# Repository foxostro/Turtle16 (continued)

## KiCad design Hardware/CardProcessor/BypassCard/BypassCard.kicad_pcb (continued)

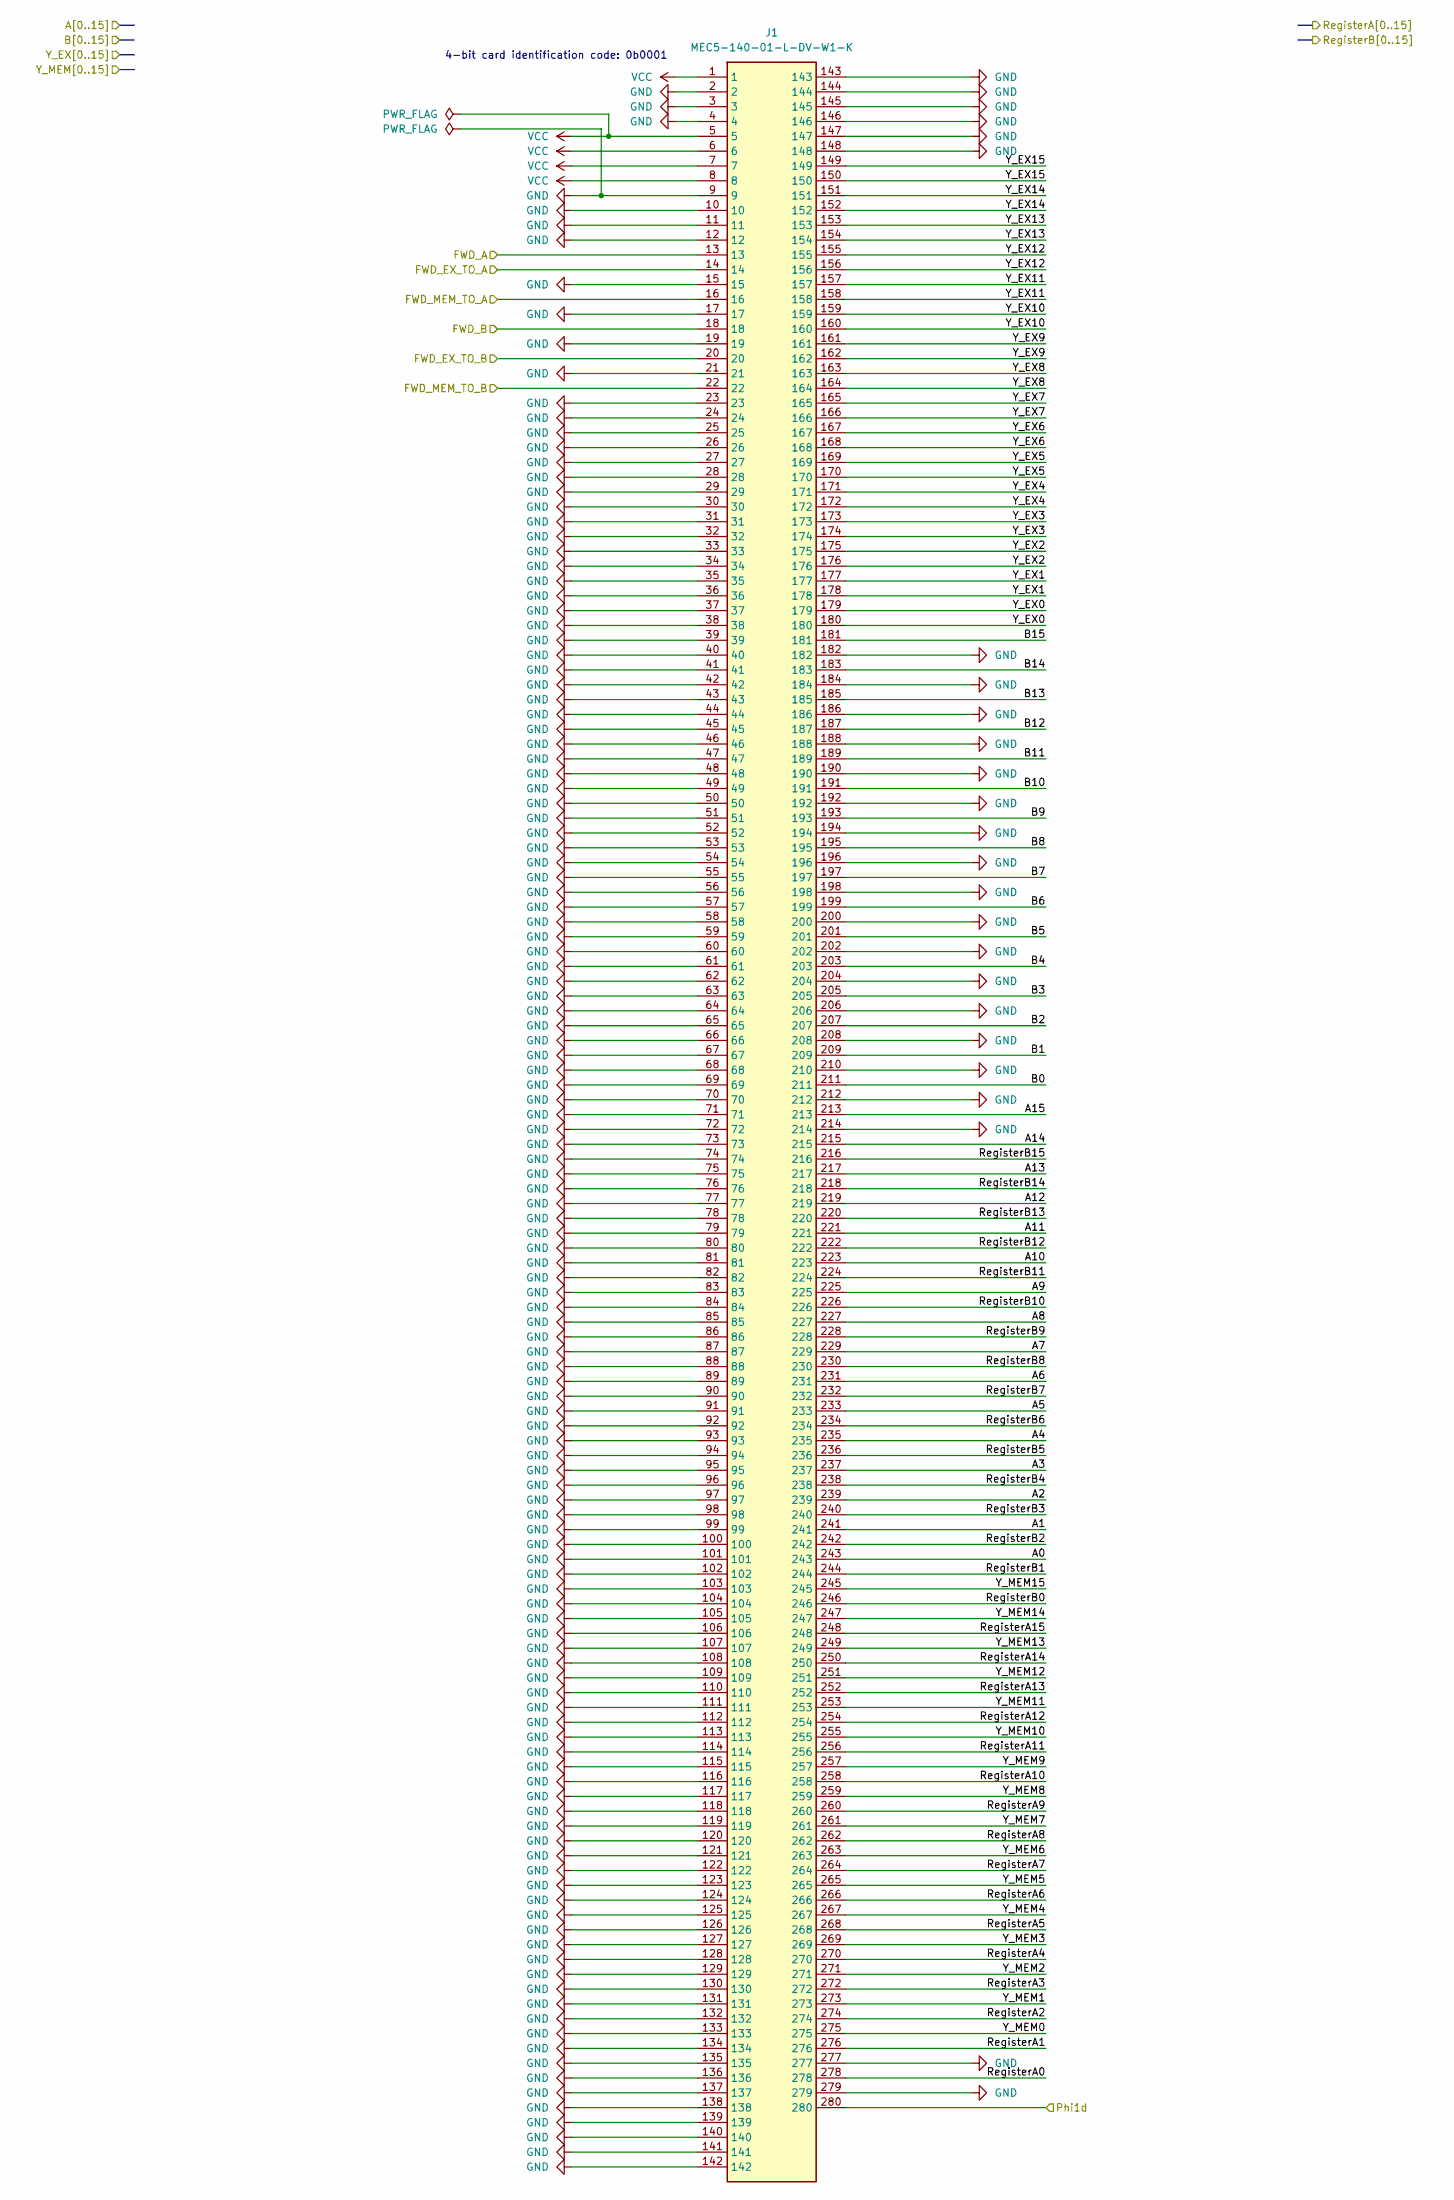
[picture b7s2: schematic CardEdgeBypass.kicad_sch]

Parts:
J1: MEC5-140-01-L-DV-W1-K; MEC5-140-01-L-DV-W1-K_Edge; Mouser Part Number 200-MEC514001LDVW1K

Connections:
/Bypass Module/A0: J1.243; also elsewhere on the board
/Bypass Module/A1: J1.241; also elsewhere on the board
/Bypass Module/A2: J1.239; also elsewhere on the board
/Bypass Module/A3: J1.237; also elsewhere on the board
/Bypass Module/A4: J1.235; also elsewhere on the board
/Bypass Module/A5: J1.233; also elsewhere on the board
/Bypass Module/A6: J1.231; also elsewhere on the board
/Bypass Module/A7: J1.229; also elsewhere on the board
/Bypass Module/A8: J1.227; also elsewhere on the board
/Bypass Module/A9: J1.225; also elsewhere on the board
/Bypass Module/A10: J1.223; also elsewhere on the board
/Bypass Module/A11: J1.221; also elsewhere on the board
/Bypass Module/A12: J1.219; also elsewhere on the board
/Bypass Module/A13: J1.217; also elsewhere on the board
/Bypass Module/A14: J1.215; also elsewhere on the board
/Bypass Module/A15: J1.213; also elsewhere on the board
/Bypass Module/B0: J1.211; also elsewhere on the board
/Bypass Module/B1: J1.209; also elsewhere on the board
/Bypass Module/B2: J1.207; also elsewhere on the board
/Bypass Module/B3: J1.205; also elsewhere on the board
/Bypass Module/B4: J1.203; also elsewhere on the board
/Bypass Module/B5: J1.201; also elsewhere on the board
/Bypass Module/B6: J1.199; also elsewhere on the board
/Bypass Module/B7: J1.197; also elsewhere on the board
/Bypass Module/B8: J1.195; also elsewhere on the board
/Bypass Module/B9: J1.193; also elsewhere on the board
/Bypass Module/B10: J1.191; also elsewhere on the board
/Bypass Module/B11: J1.189; also elsewhere on the board
/Bypass Module/B12: J1.187; also elsewhere on the board
/Bypass Module/B13: J1.185; also elsewhere on the board
/Bypass Module/B14: J1.183; also elsewhere on the board
/Bypass Module/B15: J1.181; also elsewhere on the board
/Bypass Module/FWD_A: J1.13; also elsewhere on the board
/Bypass Module/FWD_B: J1.18; also elsewhere on the board
/Bypass Module/FWD_EX_TO_A: J1.16; also elsewhere on the board
/Bypass Module/FWD_EX_TO_B: J1.20; also elsewhere on the board
/Bypass Module/FWD_MEM_TO_A: J1.14; also elsewhere on the board
/Bypass Module/FWD_MEM_TO_B: J1.22; also elsewhere on the board
/Bypass Module/Phi1d: J1.280; also elsewhere on the board
/Bypass Module/RegisterA0: J1.278; also elsewhere on the board
/Bypass Module/RegisterA1: J1.276; also elsewhere on the board
/Bypass Module/RegisterA2: J1.274; also elsewhere on the board
/Bypass Module/RegisterA3: J1.272; also elsewhere on the board
/Bypass Module/RegisterA4: J1.270; also elsewhere on the board
/Bypass Module/RegisterA5: J1.268; also elsewhere on the board
/Bypass Module/RegisterA6: J1.266; also elsewhere on the board
/Bypass Module/RegisterA7: J1.264; also elsewhere on the board
/Bypass Module/RegisterA8: J1.262; also elsewhere on the board
/Bypass Module/RegisterA9: J1.260; also elsewhere on the board
/Bypass Module/RegisterA10: J1.258; also elsewhere on the board
/Bypass Module/RegisterA11: J1.256; also elsewhere on the board
/Bypass Module/RegisterA12: J1.254; also elsewhere on the board
/Bypass Module/RegisterA13: J1.252; also elsewhere on the board
/Bypass Module/RegisterA14: J1.250; also elsewhere on the board
/Bypass Module/RegisterA15: J1.248; also elsewhere on the board
/Bypass Module/RegisterB0: J1.246; also elsewhere on the board
/Bypass Module/RegisterB1: J1.244; also elsewhere on the board
/Bypass Module/RegisterB2: J1.242; also elsewhere on the board
/Bypass Module/RegisterB3: J1.240; also elsewhere on the board
/Bypass Module/RegisterB4: J1.238; also elsewhere on the board
/Bypass Module/RegisterB5: J1.236; also elsewhere on the board
/Bypass Module/RegisterB6: J1.234; also elsewhere on the board
/Bypass Module/RegisterB7: J1.232; also elsewhere on the board
/Bypass Module/RegisterB8: J1.230; also elsewhere on the board
/Bypass Module/RegisterB9: J1.228; also elsewhere on the board
/Bypass Module/RegisterB10: J1.226; also elsewhere on the board
/Bypass Module/RegisterB11: J1.224; also elsewhere on the board
/Bypass Module/RegisterB12: J1.222; also elsewhere on the board
/Bypass Module/RegisterB13: J1.220; also elsewhere on the board
/Bypass Module/RegisterB14: J1.218; also elsewhere on the board
/Bypass Module/RegisterB15: J1.216; also elsewhere on the board
/Bypass Module/Y_EX0: J1.179, J1.180; also elsewhere on the board
/Bypass Module/Y_EX1: J1.177, J1.178; also elsewhere on the board
/Bypass Module/Y_EX2: J1.175, J1.176; also elsewhere on the board
/Bypass Module/Y_EX3: J1.173, J1.174; also elsewhere on the board
/Bypass Module/Y_EX4: J1.171, J1.172; also elsewhere on the board
/Bypass Module/Y_EX5: J1.169, J1.170; also elsewhere on the board
/Bypass Module/Y_EX6: J1.167, J1.168; also elsewhere on the board
/Bypass Module/Y_EX7: J1.165, J1.166; also elsewhere on the board
/Bypass Module/Y_EX8: J1.163, J1.164; also elsewhere on the board
/Bypass Module/Y_EX9: J1.161, J1.162; also elsewhere on the board
/Bypass Module/Y_EX10: J1.159, J1.160; also elsewhere on the board
/Bypass Module/Y_EX11: J1.157, J1.158; also elsewhere on the board
/Bypass Module/Y_EX12: J1.155, J1.156; also elsewhere on the board
/Bypass Module/Y_EX13: J1.153, J1.154; also elsewhere on the board
/Bypass Module/Y_EX14: J1.151, J1.152; also elsewhere on the board
/Bypass Module/Y_EX15: J1.149, J1.150; also elsewhere on the board
/Bypass Module/Y_MEM0: J1.275; also elsewhere on the board
/Bypass Module/Y_MEM1: J1.273; also elsewhere on the board
/Bypass Module/Y_MEM2: J1.271; also elsewhere on the board
/Bypass Module/Y_MEM3: J1.269; also elsewhere on the board
/Bypass Module/Y_MEM4: J1.267; also elsewhere on the board
/Bypass Module/Y_MEM5: J1.265; also elsewhere on the board
/Bypass Module/Y_MEM6: J1.263; also elsewhere on the board
/Bypass Module/Y_MEM7: J1.261; also elsewhere on the board
/Bypass Module/Y_MEM8: J1.259; also elsewhere on the board
/Bypass Module/Y_MEM9: J1.257; also elsewhere on the board
/Bypass Module/Y_MEM10: J1.255; also elsewhere on the board
/Bypass Module/Y_MEM11: J1.253; also elsewhere on the board
/Bypass Module/Y_MEM12: J1.251; also elsewhere on the board
/Bypass Module/Y_MEM13: J1.249; also elsewhere on the board
/Bypass Module/Y_MEM14: J1.247; also elsewhere on the board
/Bypass Module/Y_MEM15: J1.245; also elsewhere on the board
GND: J1.2, J1.3, J1.4, J1.9, J1.10, J1.11, J1.12, J1.15, J1.17, J1.19, J1.21, J1.23, J1.24, J1.25, J1.26, J1.27, J1.28, J1.29, J1.30, J1.31, J1.32, J1.33, J1.34, J1.35, J1.36, J1.37, J1.38, J1.39, J1.40, J1.41, J1.42, J1.43, J1.44, J1.45, J1.46, J1.47, J1.48, J1.49, J1.50, J1.51, J1.52, J1.53, J1.54, J1.55, J1.56, J1.57, J1.58, J1.59, J1.60, J1.61, J1.62, J1.63, J1.64, J1.65, J1.66, J1.67, J1.68, J1.69, J1.70, J1.71, J1.72, J1.73, J1.74, J1.75, J1.76, J1.77, J1.78, J1.79, J1.80, J1.81, J1.82, J1.83, J1.84, J1.85, J1.86, J1.87, J1.88, J1.89, J1.90, J1.91, J1.92, J1.93, J1.94, J1.95, J1.96, J1.97, J1.98, J1.99, J1.100, J1.101, J1.102, J1.103, J1.104, J1.105, J1.106, J1.107, J1.108, J1.109, J1.110, J1.111, J1.112, J1.113, J1.114, J1.115, J1.116, J1.117, J1.118, J1.119, J1.120, J1.121, J1.122, J1.123, J1.124, J1.125, J1.126, J1.127, J1.128, J1.129, J1.130, J1.131, J1.132, J1.133, J1.134, J1.135, J1.136, J1.137, J1.138, J1.139, J1.140, J1.141, J1.142, J1.143, J1.144, J1.145, J1.146, J1.147, J1.148, J1.182, J1.184, J1.186, J1.188, J1.190, J1.192, J1.194, J1.196, J1.198, J1.200, J1.202, J1.204, J1.206, J1.208, J1.210, J1.212, J1.214, J1.277, J1.279; also elsewhere on the board
VCC: J1.1, J1.5, J1.6, J1.7, J1.8; also elsewhere on the board

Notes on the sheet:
4-bit card identification code: 0b0001

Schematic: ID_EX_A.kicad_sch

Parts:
C7: 0.1uF; C_0603_1608Metric; Manufacturer# EMK107B7104KAHT; Mouser# 963-EMK107B7104KAHT
U7: 74ABT16374; TSSOP-48_6.1x12.5mm_P0.5mm; Manufacturer# SN74ABT16374ADGGR; Mouser# 595-SNABT16374ADGGR

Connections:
/Bypass Module/A0: U7.2 (1Q1); also elsewhere on the board
/Bypass Module/A1: U7.3 (1Q2); also elsewhere on the board
/Bypass Module/A2: U7.5 (1Q3); also elsewhere on the board
/Bypass Module/A3: U7.6 (1Q4); also elsewhere on the board
/Bypass Module/A4: U7.8 (1Q5); also elsewhere on the board
/Bypass Module/A5: U7.9 (1Q6); also elsewhere on the board
/Bypass Module/A6: U7.11 (1Q7); also elsewhere on the board
/Bypass Module/A7: U7.12 (1Q8); also elsewhere on the board
/Bypass Module/A8: U7.13 (2Q1); also elsewhere on the board
/Bypass Module/A9: U7.14 (2Q2); also elsewhere on the board
/Bypass Module/A10: U7.16 (2Q3); also elsewhere on the board
/Bypass Module/A11: U7.17 (2Q4); also elsewhere on the board
/Bypass Module/A12: U7.19 (2Q5); also elsewhere on the board
/Bypass Module/A13: U7.20 (2Q6); also elsewhere on the board
/Bypass Module/A14: U7.22 (2Q7); also elsewhere on the board
/Bypass Module/A15: U7.23 (2Q8); also elsewhere on the board
/Bypass Module/Operand Forwarding A/A_ID0: U7.47 (1D1); also elsewhere on the board
/Bypass Module/Operand Forwarding A/A_ID1: U7.46 (1D2); also elsewhere on the board
/Bypass Module/Operand Forwarding A/A_ID2: U7.44 (1D3); also elsewhere on the board
/Bypass Module/Operand Forwarding A/A_ID3: U7.43 (1D4); also elsewhere on the board
/Bypass Module/Operand Forwarding A/A_ID4: U7.41 (1D5); also elsewhere on the board
/Bypass Module/Operand Forwarding A/A_ID5: U7.40 (1D6); also elsewhere on the board
/Bypass Module/Operand Forwarding A/A_ID6: U7.38 (1D7); also elsewhere on the board
/Bypass Module/Operand Forwarding A/A_ID7: U7.37 (1D8); also elsewhere on the board
/Bypass Module/Operand Forwarding A/A_ID8: U7.36 (2D1); also elsewhere on the board
/Bypass Module/Operand Forwarding A/A_ID9: U7.35 (2D2); also elsewhere on the board
/Bypass Module/Operand Forwarding A/A_ID10: U7.33 (2D3); also elsewhere on the board
/Bypass Module/Operand Forwarding A/A_ID11: U7.32 (2D4); also elsewhere on the board
/Bypass Module/Operand Forwarding A/A_ID12: U7.30 (2D5); also elsewhere on the board
/Bypass Module/Operand Forwarding A/A_ID13: U7.29 (2D6); also elsewhere on the board
/Bypass Module/Operand Forwarding A/A_ID14: U7.27 (2D7); also elsewhere on the board
/Bypass Module/Operand Forwarding A/A_ID15: U7.26 (2D8); also elsewhere on the board
/Bypass Module/Phi1d: U7.25 (2CLK), U7.48 (1CLK); also elsewhere on the board
GND: C7.2, U7.1 (1~OE), U7.4 (GND), U7.10 (GND), U7.15 (GND), U7.21 (GND), U7.24 (2~OE), U7.28 (GND), U7.34 (GND), U7.39 (GND), U7.45 (GND); also elsewhere on the board
VCC: C7.1, U7.7 (VCC), U7.18 (VCC), U7.31 (VCC), U7.42 (VCC); also elsewhere on the board

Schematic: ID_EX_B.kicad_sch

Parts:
C8: 0.1uF; C_0603_1608Metric; Manufacturer# EMK107B7104KAHT; Mouser# 963-EMK107B7104KAHT
U8: 74ABT16374; TSSOP-48_6.1x12.5mm_P0.5mm; Manufacturer# SN74ABT16374ADGGR; Mouser# 595-SNABT16374ADGGR

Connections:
/Bypass Module/B0: U8.2 (1Q1); also elsewhere on the board
/Bypass Module/B1: U8.3 (1Q2); also elsewhere on the board
/Bypass Module/B2: U8.5 (1Q3); also elsewhere on the board
/Bypass Module/B3: U8.6 (1Q4); also elsewhere on the board
/Bypass Module/B4: U8.8 (1Q5); also elsewhere on the board
/Bypass Module/B5: U8.9 (1Q6); also elsewhere on the board
/Bypass Module/B6: U8.11 (1Q7); also elsewhere on the board
/Bypass Module/B7: U8.12 (1Q8); also elsewhere on the board
/Bypass Module/B8: U8.13 (2Q1); also elsewhere on the board
/Bypass Module/B9: U8.14 (2Q2); also elsewhere on the board
/Bypass Module/B10: U8.16 (2Q3); also elsewhere on the board
/Bypass Module/B11: U8.17 (2Q4); also elsewhere on the board
/Bypass Module/B12: U8.19 (2Q5); also elsewhere on the board
/Bypass Module/B13: U8.20 (2Q6); also elsewhere on the board
/Bypass Module/B14: U8.22 (2Q7); also elsewhere on the board
/Bypass Module/B15: U8.23 (2Q8); also elsewhere on the board
/Bypass Module/Operand Forwarding B/B_ID0: U8.47 (1D1); also elsewhere on the board
/Bypass Module/Operand Forwarding B/B_ID1: U8.46 (1D2); also elsewhere on the board
/Bypass Module/Operand Forwarding B/B_ID2: U8.44 (1D3); also elsewhere on the board
/Bypass Module/Operand Forwarding B/B_ID3: U8.43 (1D4); also elsewhere on the board
/Bypass Module/Operand Forwarding B/B_ID4: U8.41 (1D5); also elsewhere on the board
/Bypass Module/Operand Forwarding B/B_ID5: U8.40 (1D6); also elsewhere on the board
/Bypass Module/Operand Forwarding B/B_ID6: U8.38 (1D7); also elsewhere on the board
/Bypass Module/Operand Forwarding B/B_ID7: U8.37 (1D8); also elsewhere on the board
/Bypass Module/Operand Forwarding B/B_ID8: U8.36 (2D1); also elsewhere on the board
/Bypass Module/Operand Forwarding B/B_ID9: U8.35 (2D2); also elsewhere on the board
/Bypass Module/Operand Forwarding B/B_ID10: U8.33 (2D3); also elsewhere on the board
/Bypass Module/Operand Forwarding B/B_ID11: U8.32 (2D4); also elsewhere on the board
/Bypass Module/Operand Forwarding B/B_ID12: U8.30 (2D5); also elsewhere on the board
/Bypass Module/Operand Forwarding B/B_ID13: U8.29 (2D6); also elsewhere on the board
/Bypass Module/Operand Forwarding B/B_ID14: U8.27 (2D7); also elsewhere on the board
/Bypass Module/Operand Forwarding B/B_ID15: U8.26 (2D8); also elsewhere on the board
/Bypass Module/Phi1d: U8.25 (2CLK), U8.48 (1CLK); also elsewhere on the board
GND: C8.2, U8.1 (1~OE), U8.4 (GND), U8.10 (GND), U8.15 (GND), U8.21 (GND), U8.24 (2~OE), U8.28 (GND), U8.34 (GND), U8.39 (GND), U8.45 (GND); also elsewhere on the board
VCC: C8.1, U8.7 (VCC), U8.18 (VCC), U8.31 (VCC), U8.42 (VCC); also elsewhere on the board

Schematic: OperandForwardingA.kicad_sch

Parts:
C1, C2, C3: 0.1uF; C_0603_1608Metric; Manufacturer# EMK107B7104KAHT; Mouser# 963-EMK107B7104KAHT
U1, U2, U3: 74ABT16245; TSSOP-48_6.1x12.5mm_P0.5mm; Manufacturer# SN74ABTH16245DGGR; Mouser# 595-SNABTH16245DGGR

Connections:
/Bypass Module/FWD_A: U1.25 (2~OE), U1.48 (1~OE); also elsewhere on the board
/Bypass Module/FWD_EX_TO_A: U2.25 (2~OE), U2.48 (1~OE); also elsewhere on the board
/Bypass Module/FWD_MEM_TO_A: U3.25 (2~OE), U3.48 (1~OE); also elsewhere on the board
/Bypass Module/Operand Forwarding A/A_ID0: U1.2 (1B1), U2.2 (1B1), U3.2 (1B1); also elsewhere on the board
/Bypass Module/Operand Forwarding A/A_ID1: U1.3 (1B2), U2.3 (1B2), U3.3 (1B2); also elsewhere on the board
/Bypass Module/Operand Forwarding A/A_ID2: U1.5 (1B3), U2.5 (1B3), U3.5 (1B3); also elsewhere on the board
/Bypass Module/Operand Forwarding A/A_ID3: U1.6 (1B4), U2.6 (1B4), U3.6 (1B4); also elsewhere on the board
/Bypass Module/Operand Forwarding A/A_ID4: U1.8 (1B5), U2.8 (1B5), U3.8 (1B5); also elsewhere on the board
/Bypass Module/Operand Forwarding A/A_ID5: U1.9 (1B6), U2.9 (1B6), U3.9 (1B6); also elsewhere on the board
/Bypass Module/Operand Forwarding A/A_ID6: U1.11 (1B7), U2.11 (1B7), U3.11 (1B7); also elsewhere on the board
/Bypass Module/Operand Forwarding A/A_ID7: U1.12 (1B8), U2.12 (1B8), U3.12 (1B8); also elsewhere on the board
/Bypass Module/Operand Forwarding A/A_ID8: U1.13 (2B1), U2.13 (2B1), U3.13 (2B1); also elsewhere on the board
/Bypass Module/Operand Forwarding A/A_ID9: U1.14 (2B2), U2.14 (2B2), U3.14 (2B2); also elsewhere on the board
/Bypass Module/Operand Forwarding A/A_ID10: U1.16 (2B3), U2.16 (2B3), U3.16 (2B3); also elsewhere on the board
/Bypass Module/Operand Forwarding A/A_ID11: U1.17 (2B4), U2.17 (2B4), U3.17 (2B4); also elsewhere on the board
/Bypass Module/Operand Forwarding A/A_ID12: U1.19 (2B5), U2.19 (2B5), U3.19 (2B5); also elsewhere on the board
/Bypass Module/Operand Forwarding A/A_ID13: U1.20 (2B6), U2.20 (2B6), U3.20 (2B6); also elsewhere on the board
/Bypass Module/Operand Forwarding A/A_ID14: U1.22 (2B7), U2.22 (2B7), U3.22 (2B7); also elsewhere on the board
/Bypass Module/Operand Forwarding A/A_ID15: U1.23 (2B8), U2.23 (2B8), U3.23 (2B8); also elsewhere on the board
/Bypass Module/RegisterA0: U1.47 (1A1); also elsewhere on the board
/Bypass Module/RegisterA1: U1.46 (1A2); also elsewhere on the board
/Bypass Module/RegisterA2: U1.44 (1A3); also elsewhere on the board
/Bypass Module/RegisterA3: U1.43 (1A4); also elsewhere on the board
/Bypass Module/RegisterA4: U1.41 (1A5); also elsewhere on the board
/Bypass Module/RegisterA5: U1.40 (1A6); also elsewhere on the board
/Bypass Module/RegisterA6: U1.38 (1A7); also elsewhere on the board
/Bypass Module/RegisterA7: U1.37 (1A8); also elsewhere on the board
/Bypass Module/RegisterA8: U1.36 (2A1); also elsewhere on the board
/Bypass Module/RegisterA9: U1.35 (2A2); also elsewhere on the board
/Bypass Module/RegisterA10: U1.33 (2A3); also elsewhere on the board
/Bypass Module/RegisterA11: U1.32 (2A4); also elsewhere on the board
/Bypass Module/RegisterA12: U1.30 (2A5); also elsewhere on the board
/Bypass Module/RegisterA13: U1.29 (2A6); also elsewhere on the board
/Bypass Module/RegisterA14: U1.27 (2A7); also elsewhere on the board
/Bypass Module/RegisterA15: U1.26 (2A8); also elsewhere on the board
/Bypass Module/Y_EX0: U2.47 (1A1); also elsewhere on the board
/Bypass Module/Y_EX1: U2.46 (1A2); also elsewhere on the board
/Bypass Module/Y_EX2: U2.44 (1A3); also elsewhere on the board
/Bypass Module/Y_EX3: U2.43 (1A4); also elsewhere on the board
/Bypass Module/Y_EX4: U2.41 (1A5); also elsewhere on the board
/Bypass Module/Y_EX5: U2.40 (1A6); also elsewhere on the board
/Bypass Module/Y_EX6: U2.38 (1A7); also elsewhere on the board
/Bypass Module/Y_EX7: U2.37 (1A8); also elsewhere on the board
/Bypass Module/Y_EX8: U2.36 (2A1); also elsewhere on the board
/Bypass Module/Y_EX9: U2.35 (2A2); also elsewhere on the board
/Bypass Module/Y_EX10: U2.33 (2A3); also elsewhere on the board
/Bypass Module/Y_EX11: U2.32 (2A4); also elsewhere on the board
/Bypass Module/Y_EX12: U2.30 (2A5); also elsewhere on the board
/Bypass Module/Y_EX13: U2.29 (2A6); also elsewhere on the board
/Bypass Module/Y_EX14: U2.27 (2A7); also elsewhere on the board
/Bypass Module/Y_EX15: U2.26 (2A8); also elsewhere on the board
/Bypass Module/Y_MEM0: U3.47 (1A1); also elsewhere on the board
/Bypass Module/Y_MEM1: U3.46 (1A2); also elsewhere on the board
/Bypass Module/Y_MEM2: U3.44 (1A3); also elsewhere on the board
/Bypass Module/Y_MEM3: U3.43 (1A4); also elsewhere on the board
/Bypass Module/Y_MEM4: U3.41 (1A5); also elsewhere on the board
/Bypass Module/Y_MEM5: U3.40 (1A6); also elsewhere on the board
/Bypass Module/Y_MEM6: U3.38 (1A7); also elsewhere on the board
/Bypass Module/Y_MEM7: U3.37 (1A8); also elsewhere on the board
/Bypass Module/Y_MEM8: U3.36 (2A1); also elsewhere on the board
/Bypass Module/Y_MEM9: U3.35 (2A2); also elsewhere on the board
/Bypass Module/Y_MEM10: U3.33 (2A3); also elsewhere on the board
/Bypass Module/Y_MEM11: U3.32 (2A4); also elsewhere on the board
/Bypass Module/Y_MEM12: U3.30 (2A5); also elsewhere on the board
/Bypass Module/Y_MEM13: U3.29 (2A6); also elsewhere on the board
/Bypass Module/Y_MEM14: U3.27 (2A7); also elsewhere on the board
/Bypass Module/Y_MEM15: U3.26 (2A8); also elsewhere on the board
GND: C1.2, C2.2, C3.2, U1.4 (GND), U1.10 (GND), U1.15 (GND), U1.21 (GND), U1.28 (GND), U1.34 (GND), U1.39 (GND), U1.45 (GND), U2.4 (GND), U2.10 (GND), U2.15 (GND), U2.21 (GND), U2.28 (GND), U2.34 (GND), U2.39 (GND), U2.45 (GND), U3.4 (GND), U3.10 (GND), U3.15 (GND), U3.21 (GND), U3.28 (GND), U3.34 (GND), U3.39 (GND), U3.45 (GND); also elsewhere on the board
VCC: C1.1, C2.1, C3.1, U1.1 (1DIR), U1.7 (VCC), U1.18 (VCC), U1.24 (2DIR), U1.31 (VCC), U1.42 (VCC), U2.1 (1DIR), U2.7 (VCC), U2.18 (VCC), U2.24 (2DIR), U2.31 (VCC), U2.42 (VCC), U3.1 (1DIR), U3.7 (VCC), U3.18 (VCC), U3.24 (2DIR), U3.31 (VCC), U3.42 (VCC); also elsewhere on the board

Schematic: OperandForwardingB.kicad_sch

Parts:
C4, C5, C6: 0.1uF; C_0603_1608Metric; Manufacturer# EMK107B7104KAHT; Mouser# 963-EMK107B7104KAHT
U4, U5, U6: 74ABT16245; TSSOP-48_6.1x12.5mm_P0.5mm; Manufacturer# SN74ABTH16245DGGR; Mouser# 595-SNABTH16245DGGR

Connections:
/Bypass Module/FWD_B: U4.25 (2~OE), U4.48 (1~OE); also elsewhere on the board
/Bypass Module/FWD_EX_TO_B: U5.25 (2~OE), U5.48 (1~OE); also elsewhere on the board
/Bypass Module/FWD_MEM_TO_B: U6.25 (2~OE), U6.48 (1~OE); also elsewhere on the board
/Bypass Module/Operand Forwarding B/B_ID0: U4.2 (1B1), U5.2 (1B1), U6.2 (1B1); also elsewhere on the board
/Bypass Module/Operand Forwarding B/B_ID1: U4.3 (1B2), U5.3 (1B2), U6.3 (1B2); also elsewhere on the board
/Bypass Module/Operand Forwarding B/B_ID2: U4.5 (1B3), U5.5 (1B3), U6.5 (1B3); also elsewhere on the board
/Bypass Module/Operand Forwarding B/B_ID3: U4.6 (1B4), U5.6 (1B4), U6.6 (1B4); also elsewhere on the board
/Bypass Module/Operand Forwarding B/B_ID4: U4.8 (1B5), U5.8 (1B5), U6.8 (1B5); also elsewhere on the board
/Bypass Module/Operand Forwarding B/B_ID5: U4.9 (1B6), U5.9 (1B6), U6.9 (1B6); also elsewhere on the board
/Bypass Module/Operand Forwarding B/B_ID6: U4.11 (1B7), U5.11 (1B7), U6.11 (1B7); also elsewhere on the board
/Bypass Module/Operand Forwarding B/B_ID7: U4.12 (1B8), U5.12 (1B8), U6.12 (1B8); also elsewhere on the board
/Bypass Module/Operand Forwarding B/B_ID8: U4.13 (2B1), U5.13 (2B1), U6.13 (2B1); also elsewhere on the board
/Bypass Module/Operand Forwarding B/B_ID9: U4.14 (2B2), U5.14 (2B2), U6.14 (2B2); also elsewhere on the board
/Bypass Module/Operand Forwarding B/B_ID10: U4.16 (2B3), U5.16 (2B3), U6.16 (2B3); also elsewhere on the board
/Bypass Module/Operand Forwarding B/B_ID11: U4.17 (2B4), U5.17 (2B4), U6.17 (2B4); also elsewhere on the board
/Bypass Module/Operand Forwarding B/B_ID12: U4.19 (2B5), U5.19 (2B5), U6.19 (2B5); also elsewhere on the board
/Bypass Module/Operand Forwarding B/B_ID13: U4.20 (2B6), U5.20 (2B6), U6.20 (2B6); also elsewhere on the board
/Bypass Module/Operand Forwarding B/B_ID14: U4.22 (2B7), U5.22 (2B7), U6.22 (2B7); also elsewhere on the board
/Bypass Module/Operand Forwarding B/B_ID15: U4.23 (2B8), U5.23 (2B8), U6.23 (2B8); also elsewhere on the board
/Bypass Module/RegisterB0: U4.47 (1A1); also elsewhere on the board
/Bypass Module/RegisterB1: U4.46 (1A2); also elsewhere on the board
/Bypass Module/RegisterB2: U4.44 (1A3); also elsewhere on the board
/Bypass Module/RegisterB3: U4.43 (1A4); also elsewhere on the board
/Bypass Module/RegisterB4: U4.41 (1A5); also elsewhere on the board
/Bypass Module/RegisterB5: U4.40 (1A6); also elsewhere on the board
/Bypass Module/RegisterB6: U4.38 (1A7); also elsewhere on the board
/Bypass Module/RegisterB7: U4.37 (1A8); also elsewhere on the board
/Bypass Module/RegisterB8: U4.36 (2A1); also elsewhere on the board
/Bypass Module/RegisterB9: U4.35 (2A2); also elsewhere on the board
/Bypass Module/RegisterB10: U4.33 (2A3); also elsewhere on the board
/Bypass Module/RegisterB11: U4.32 (2A4); also elsewhere on the board
/Bypass Module/RegisterB12: U4.30 (2A5); also elsewhere on the board
/Bypass Module/RegisterB13: U4.29 (2A6); also elsewhere on the board
/Bypass Module/RegisterB14: U4.27 (2A7); also elsewhere on the board
/Bypass Module/RegisterB15: U4.26 (2A8); also elsewhere on the board
/Bypass Module/Y_EX0: U5.47 (1A1); also elsewhere on the board
/Bypass Module/Y_EX1: U5.46 (1A2); also elsewhere on the board
/Bypass Module/Y_EX2: U5.44 (1A3); also elsewhere on the board
/Bypass Module/Y_EX3: U5.43 (1A4); also elsewhere on the board
/Bypass Module/Y_EX4: U5.41 (1A5); also elsewhere on the board
/Bypass Module/Y_EX5: U5.40 (1A6); also elsewhere on the board
/Bypass Module/Y_EX6: U5.38 (1A7); also elsewhere on the board
/Bypass Module/Y_EX7: U5.37 (1A8); also elsewhere on the board
/Bypass Module/Y_EX8: U5.36 (2A1); also elsewhere on the board
/Bypass Module/Y_EX9: U5.35 (2A2); also elsewhere on the board
/Bypass Module/Y_EX10: U5.33 (2A3); also elsewhere on the board
/Bypass Module/Y_EX11: U5.32 (2A4); also elsewhere on the board
/Bypass Module/Y_EX12: U5.30 (2A5); also elsewhere on the board
/Bypass Module/Y_EX13: U5.29 (2A6); also elsewhere on the board
/Bypass Module/Y_EX14: U5.27 (2A7); also elsewhere on the board
/Bypass Module/Y_EX15: U5.26 (2A8); also elsewhere on the board
/Bypass Module/Y_MEM0: U6.47 (1A1); also elsewhere on the board
/Bypass Module/Y_MEM1: U6.46 (1A2); also elsewhere on the board
/Bypass Module/Y_MEM2: U6.44 (1A3); also elsewhere on the board
/Bypass Module/Y_MEM3: U6.43 (1A4); also elsewhere on the board
/Bypass Module/Y_MEM4: U6.41 (1A5); also elsewhere on the board
/Bypass Module/Y_MEM5: U6.40 (1A6); also elsewhere on the board
/Bypass Module/Y_MEM6: U6.38 (1A7); also elsewhere on the board
/Bypass Module/Y_MEM7: U6.37 (1A8); also elsewhere on the board
/Bypass Module/Y_MEM8: U6.36 (2A1); also elsewhere on the board
/Bypass Module/Y_MEM9: U6.35 (2A2); also elsewhere on the board
/Bypass Module/Y_MEM10: U6.33 (2A3); also elsewhere on the board
/Bypass Module/Y_MEM11: U6.32 (2A4); also elsewhere on the board
/Bypass Module/Y_MEM12: U6.30 (2A5); also elsewhere on the board
/Bypass Module/Y_MEM13: U6.29 (2A6); also elsewhere on the board
/Bypass Module/Y_MEM14: U6.27 (2A7); also elsewhere on the board
/Bypass Module/Y_MEM15: U6.26 (2A8); also elsewhere on the board
GND: C4.2, C5.2, C6.2, U4.4 (GND), U4.10 (GND), U4.15 (GND), U4.21 (GND), U4.28 (GND), U4.34 (GND), U4.39 (GND), U4.45 (GND), U5.4 (GND), U5.10 (GND), U5.15 (GND), U5.21 (GND), U5.28 (GND), U5.34 (GND), U5.39 (GND), U5.45 (GND), U6.4 (GND), U6.10 (GND), U6.15 (GND), U6.21 (GND), U6.28 (GND), U6.34 (GND), U6.39 (GND), U6.45 (GND); also elsewhere on the board
VCC: C4.1, C5.1, C6.1, U4.1 (1DIR), U4.7 (VCC), U4.18 (VCC), U4.24 (2DIR), U4.31 (VCC), U4.42 (VCC), U5.1 (1DIR), U5.7 (VCC), U5.18 (VCC), U5.24 (2DIR), U5.31 (VCC), U5.42 (VCC), U6.1 (1DIR), U6.7 (VCC), U6.18 (VCC), U6.24 (2DIR), U6.31 (VCC), U6.42 (VCC); also elsewhere on the board

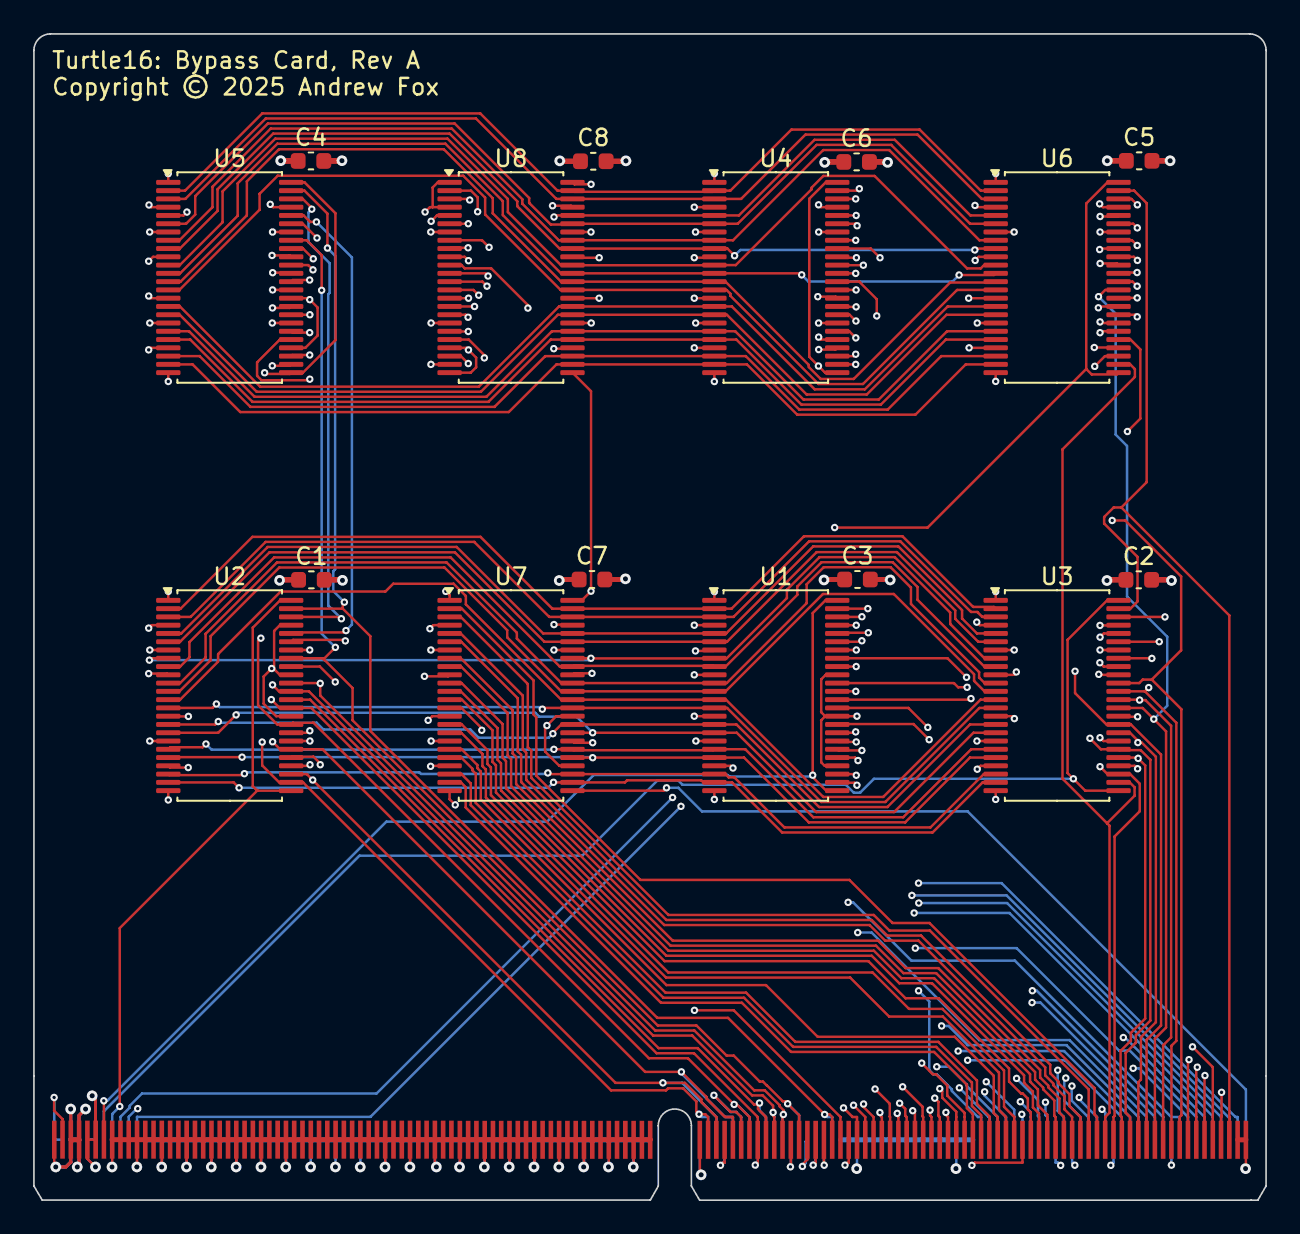
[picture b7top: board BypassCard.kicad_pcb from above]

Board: 6 copper layers, 74.5 x 70.5 mm, 17 parts (0 on the bottom side), 137 nets.
